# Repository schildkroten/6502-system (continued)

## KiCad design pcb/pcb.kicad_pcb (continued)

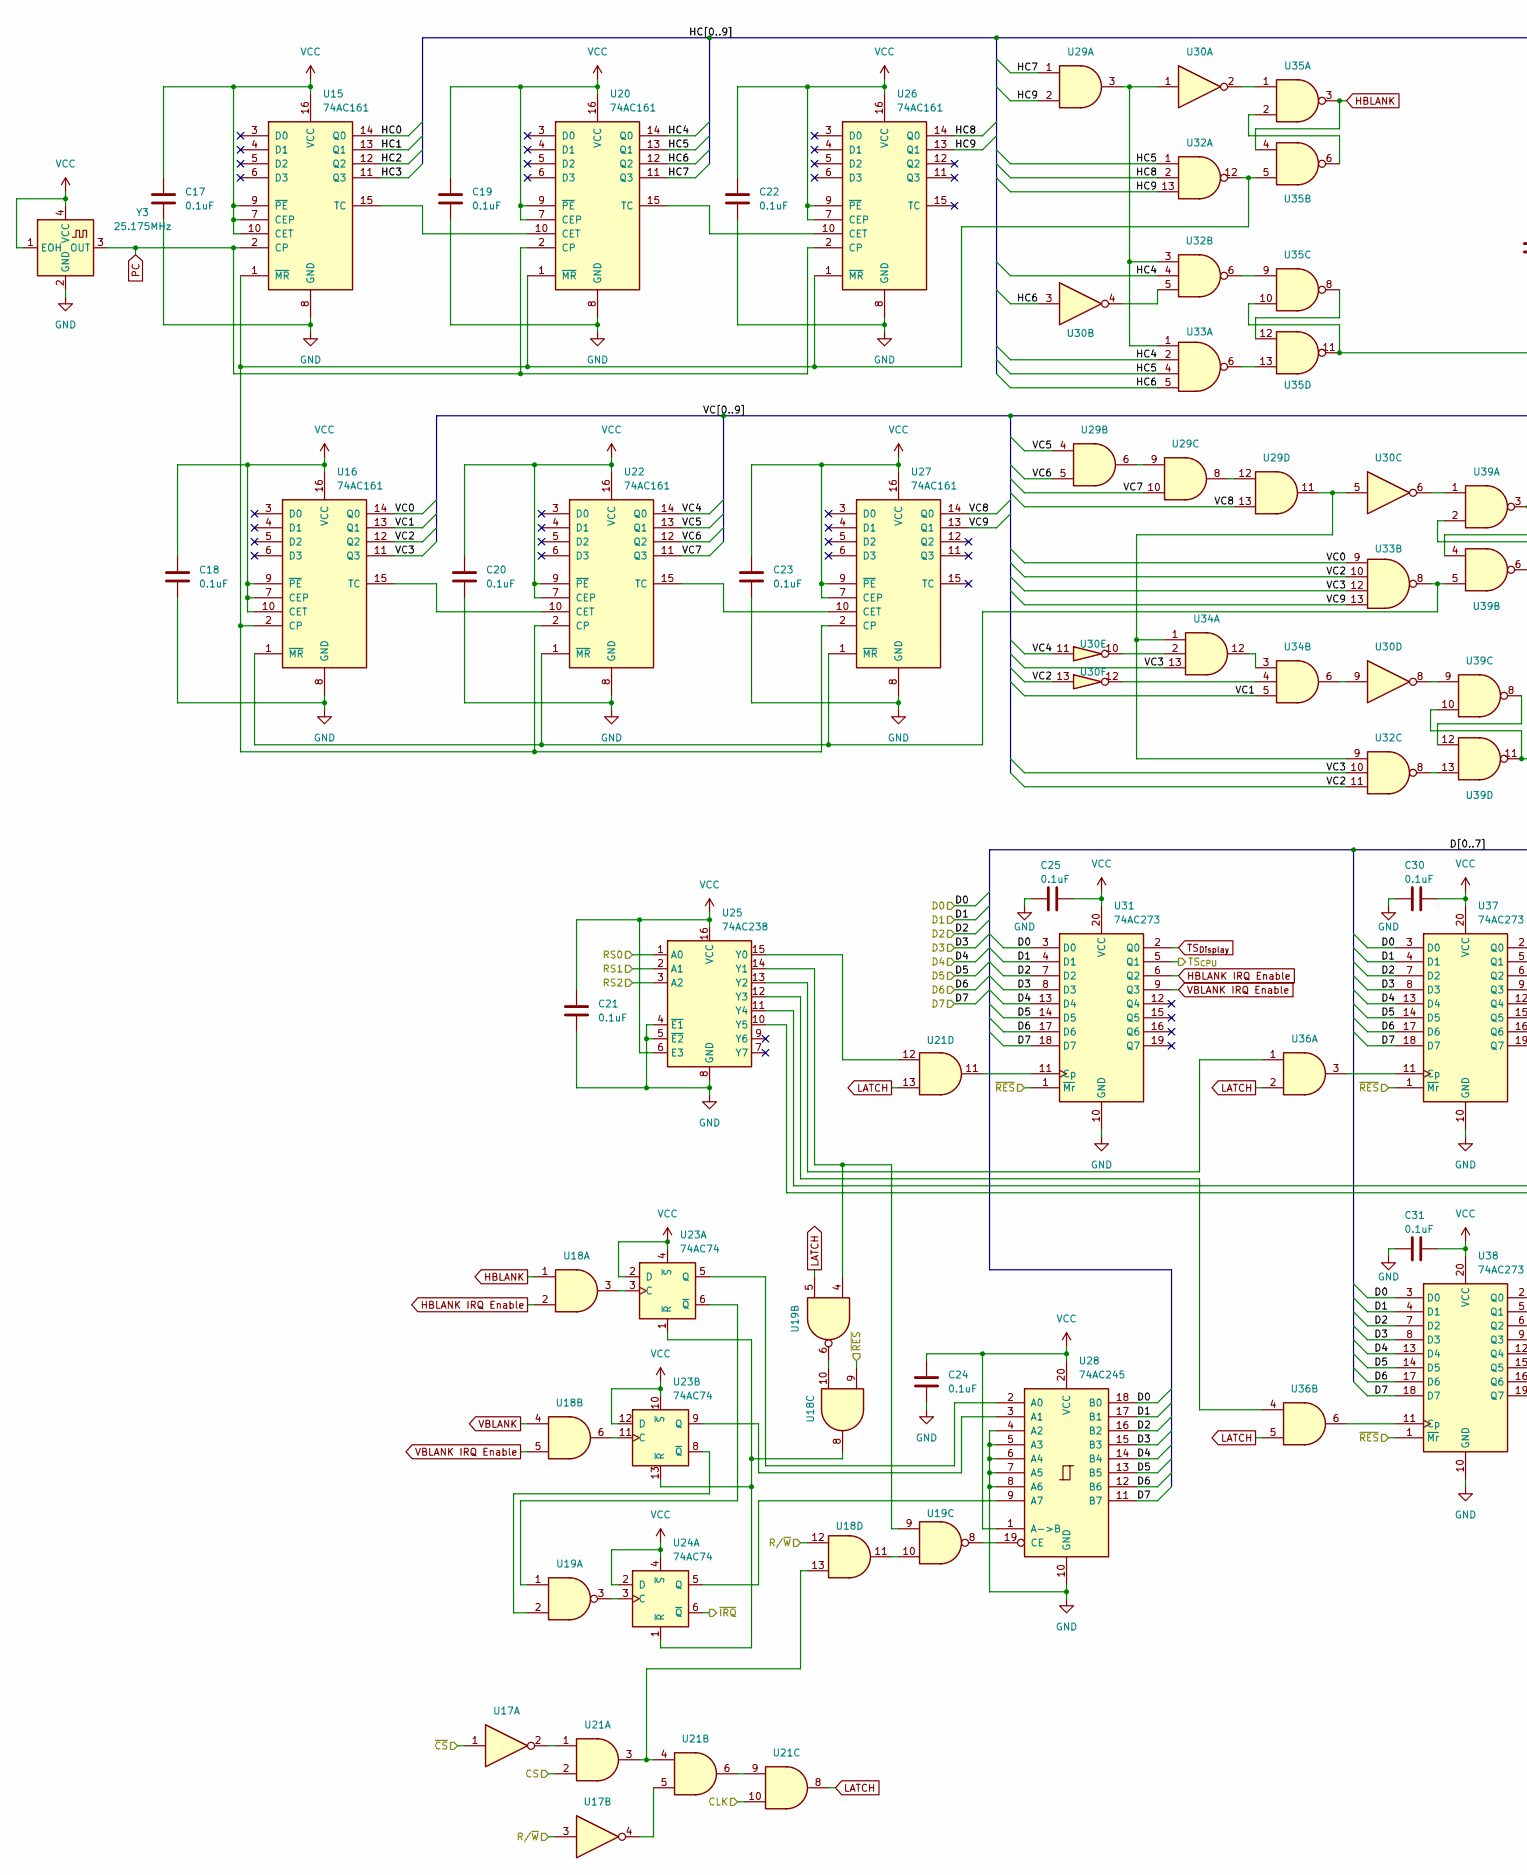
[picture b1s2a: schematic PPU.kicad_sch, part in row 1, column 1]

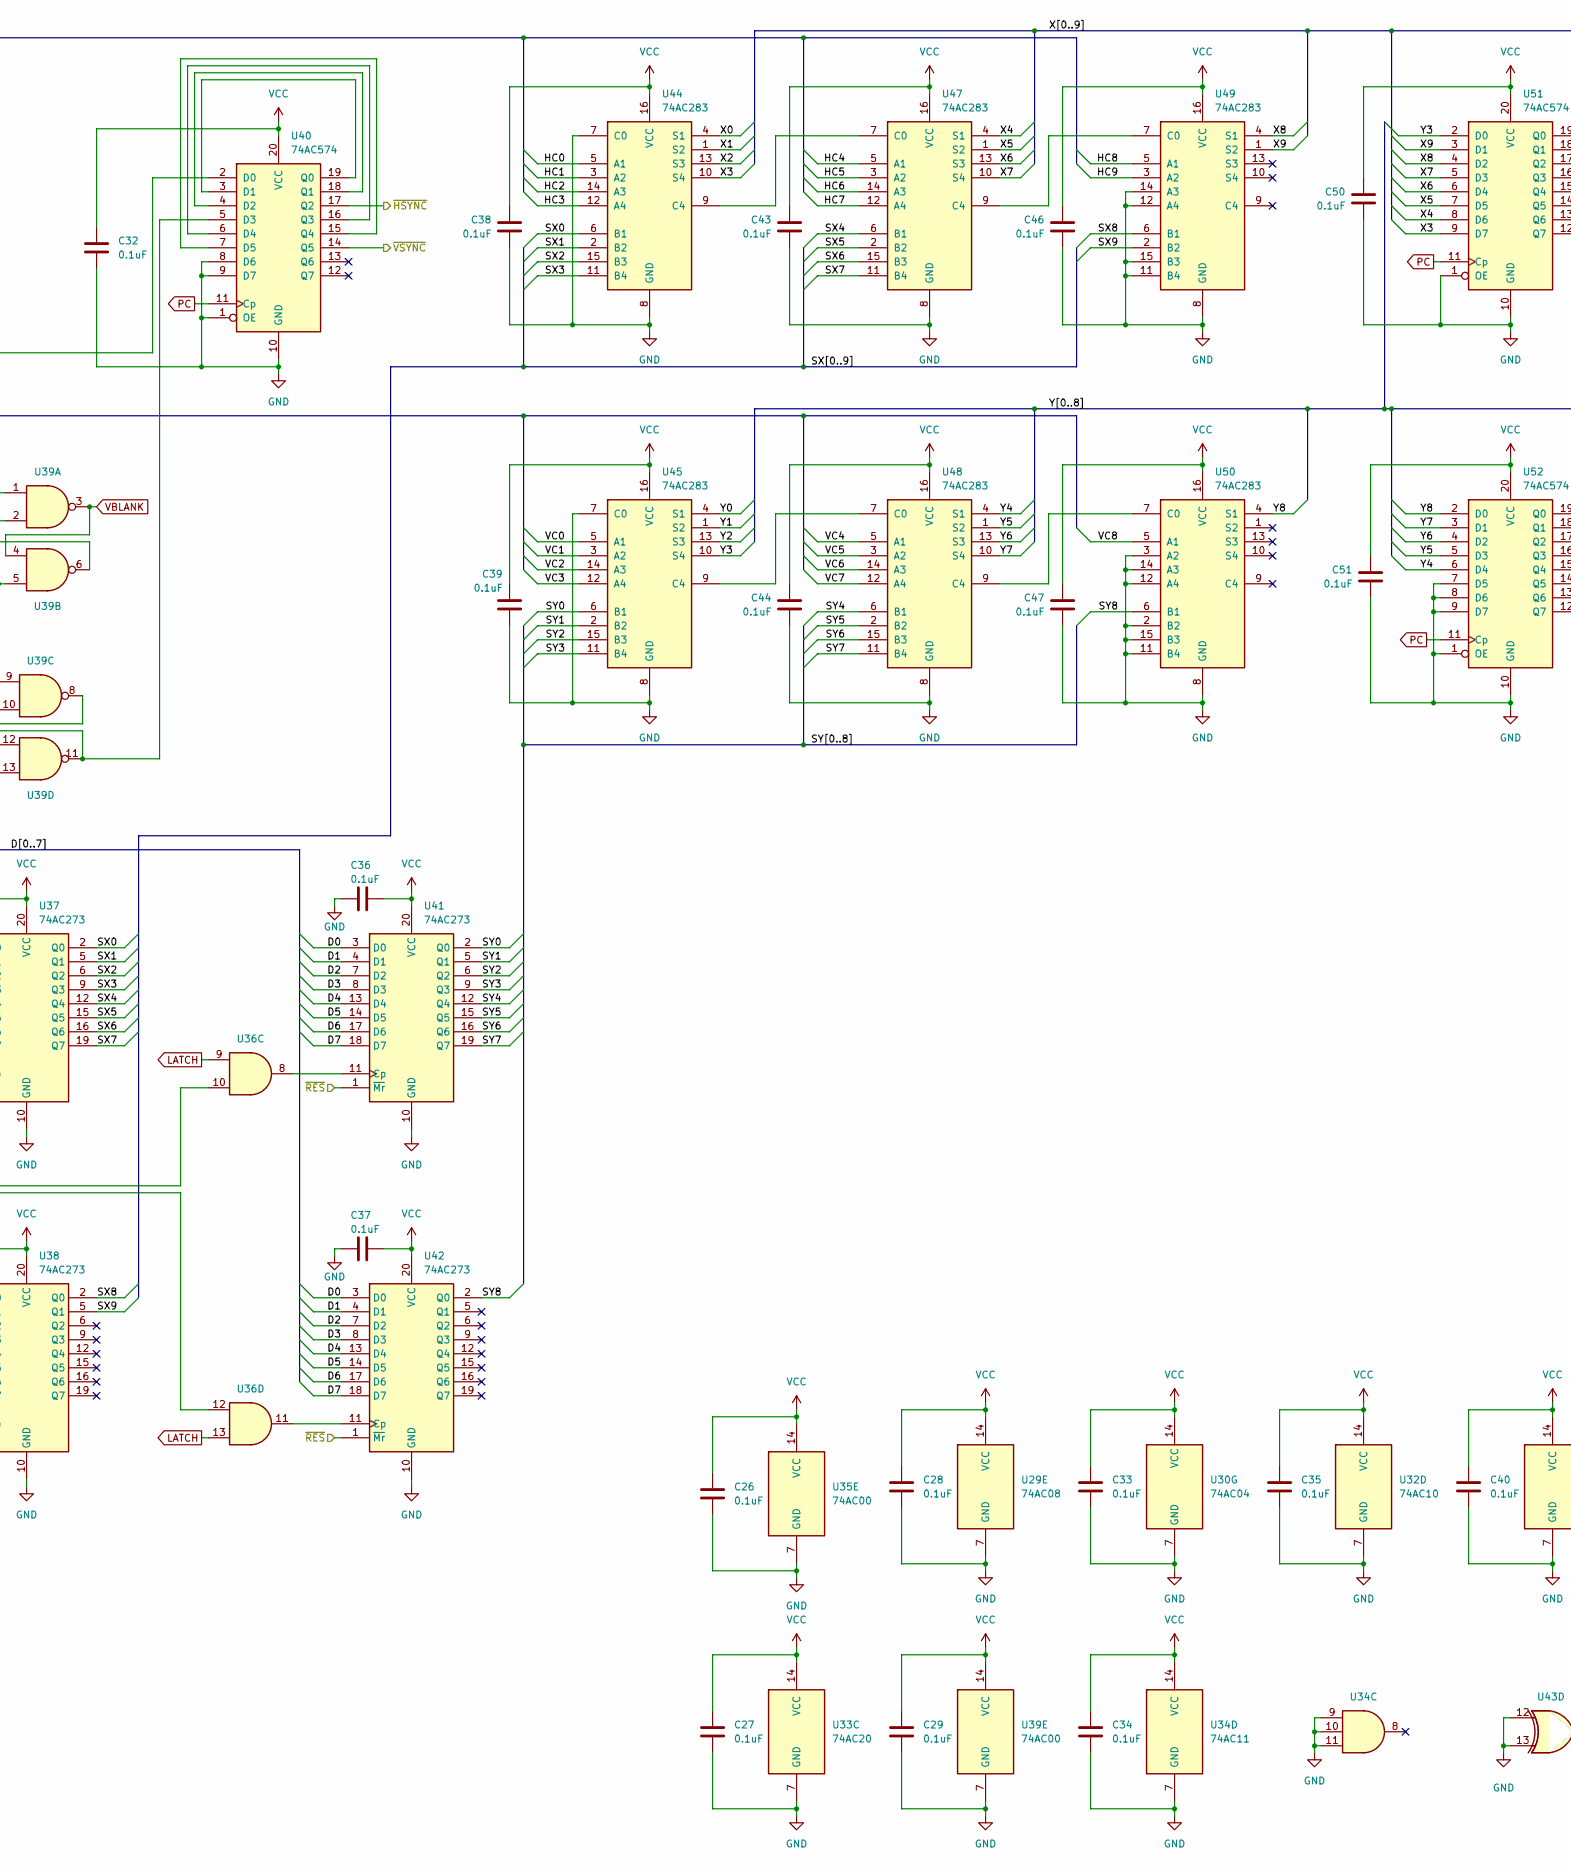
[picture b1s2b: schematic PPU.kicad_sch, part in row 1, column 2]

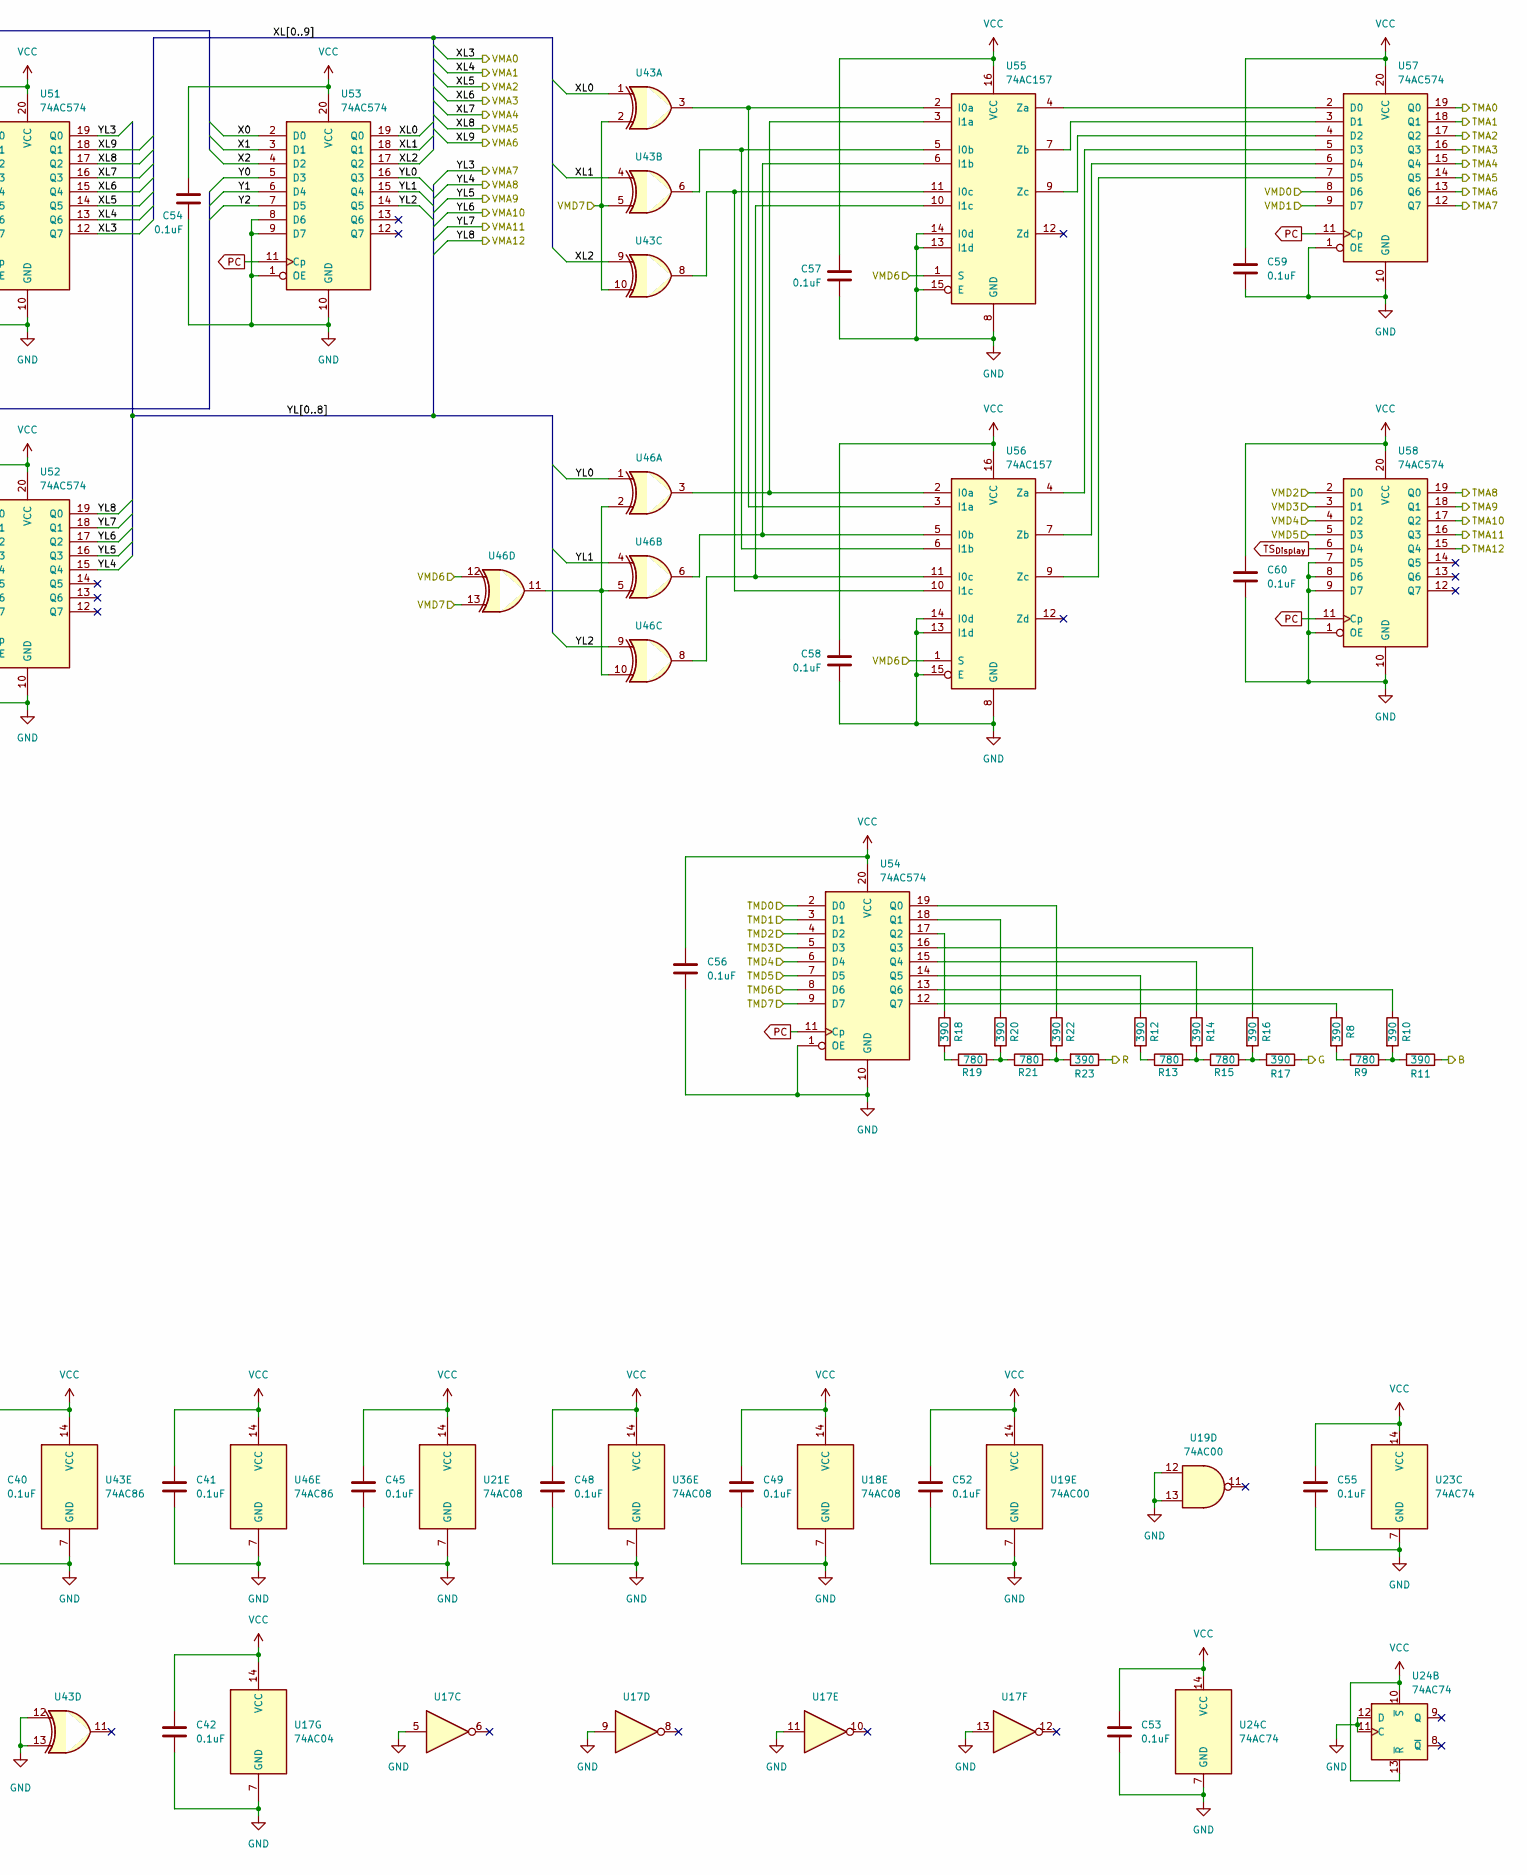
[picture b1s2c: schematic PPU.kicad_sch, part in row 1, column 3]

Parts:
C17, C18, C19, C20, C21, C22, C23, C24, C25, C26, C27, C28, C29, C30, C31, C32, C33, C34, C35, C36, C37, C38, C39, C40, C41, C42, C43, C44, C45, C46, C47, C48, C49, C50, C51, C52, C53, C54, C55, C56, C57, C58, C59, C60: 0.1uF; C_0805_2012Metric
R8, R10, R11, R12, R14, R16, R17, R18, R20, R22, R23: 390; R_0805_2012Metric
R9, R13, R15, R19, R21: 780; R_0805_2012Metric
U15, U16, U20, U22, U26, U27: 74AC161; SOIC-16_3.9x9.9mm_P1.27mm
U17, U30: 74AC04; SOIC-14_3.9x8.7mm_P1.27mm
U18, U21, U29, U36: 74AC08; SOIC-14_3.9x8.7mm_P1.27mm
U19, U35, U39: 74AC00; SOIC-14_3.9x8.7mm_P1.27mm
U23, U24: 74AC74; SOIC-14_3.9x8.7mm_P1.27mm
U25: 74AC238; SOIC-16_3.9x9.9mm_P1.27mm
U28: 74AC245; TSSOP-20_4.4x6.5mm_P0.65mm
U31, U37, U38, U41, U42: 74AC273; SOIC-20W_7.5x12.8mm_P1.27mm
U32: 74AC10; SOIC-14_3.9x8.7mm_P1.27mm
U33: 74AC20; SOIC-14_3.9x8.7mm_P1.27mm
U34: 74AC11; SOIC-14_3.9x8.7mm_P1.27mm
U40, U51, U52, U53, U54, U57, U58: 74AC574; SOIC-20W_7.5x12.8mm_P1.27mm
U43, U46: 74AC86; SOIC-14_3.9x8.7mm_P1.27mm
U44, U45, U47, U48, U49, U50: 74AC283; SOIC-16_3.9x9.9mm_P1.27mm
U55, U56: 74AC157; SOIC-16_3.9x9.9mm_P1.27mm
Y3: 25.175MHz; Oscillator_SMD_SeikoEpson_SG8002CA-4Pin_7.0x5.0mm

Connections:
/A0: U25.1 (A0); also elsewhere on the board
/A1: U25.2 (A1); also elsewhere on the board
/A2: U25.3 (A2); also elsewhere on the board
/D0: U28.18 (B0), U31.3 (D0), U37.3 (D0), U38.3 (D0), U41.3 (D0), U42.3 (D0); also elsewhere on the board
/D1: U28.17 (B1), U31.4 (D1), U37.4 (D1), U38.4 (D1), U41.4 (D1), U42.4 (D1); also elsewhere on the board
/D2: U28.16 (B2), U31.7 (D2), U37.7 (D2), U38.7 (D2), U41.7 (D2), U42.7 (D2); also elsewhere on the board
/D3: U28.15 (B3), U31.8 (D3), U37.8 (D3), U38.8 (D3), U41.8 (D3), U42.8 (D3); also elsewhere on the board
/D4: U28.14 (B4), U31.13 (D4), U37.13 (D4), U38.13 (D4), U41.13 (D4), U42.13 (D4); also elsewhere on the board
/D5: U28.13 (B5), U31.14 (D5), U37.14 (D5), U38.14 (D5), U41.14 (D5), U42.14 (D5); also elsewhere on the board
/D6: U28.12 (B6), U31.17 (D6), U37.17 (D6), U38.17 (D6), U41.17 (D6), U42.17 (D6); also elsewhere on the board
/D7: U28.11 (B7), U31.18 (D7), U37.18 (D7), U38.18 (D7), U41.18 (D7), U42.18 (D7); also elsewhere on the board
/PPU/B: R11.1; also elsewhere on the board
/PPU/G: R17.1; also elsewhere on the board
/PPU/HC0: U15.14 (Q0), U44.5 (A1)
/PPU/HC1: U15.13 (Q1), U44.3 (A2)
/PPU/HC2: U15.12 (Q2), U44.14 (A3)
/PPU/HC3: U15.11 (Q3), U44.12 (A4)
/PPU/HC4: U20.14 (Q0), U32.4, U33.2, U47.5 (A1)
/PPU/HC5: U20.13 (Q1), U32.1, U33.4, U47.3 (A2)
/PPU/HC6: U20.12 (Q2), U30.3, U33.5, U47.14 (A3)
/PPU/HC7: U20.11 (Q3), U29.1, U47.12 (A4)
/PPU/HC8: U26.14 (Q0), U32.2, U49.5 (A1)
/PPU/HC9: U26.13 (Q1), U29.2, U32.13, U49.3 (A2)
/PPU/R: R23.1; also elsewhere on the board
/PPU/SX0: U37.2 (Q0), U44.6 (B1)
/PPU/SX1: U37.5 (Q1), U44.2 (B2)
/PPU/SX2: U37.6 (Q2), U44.15 (B3)
/PPU/SX3: U37.9 (Q3), U44.11 (B4)
/PPU/SX4: U37.12 (Q4), U47.6 (B1)
/PPU/SX5: U37.15 (Q5), U47.2 (B2)
/PPU/SX6: U37.16 (Q6), U47.15 (B3)
/PPU/SX7: U37.19 (Q7), U47.11 (B4)
/PPU/SX8: U38.2 (Q0), U49.6 (B1)
/PPU/SX9: U38.5 (Q1), U49.2 (B2)
/PPU/SY0: U41.2 (Q0), U45.6 (B1)
/PPU/SY1: U41.5 (Q1), U45.2 (B2)
/PPU/SY2: U41.6 (Q2), U45.15 (B3)
/PPU/SY3: U41.9 (Q3), U45.11 (B4)
/PPU/SY4: U41.12 (Q4), U48.6 (B1)
/PPU/SY5: U41.15 (Q5), U48.2 (B2)
/PPU/SY6: U41.16 (Q6), U48.15 (B3)
/PPU/SY7: U41.19 (Q7), U48.11 (B4)
/PPU/SY8: U42.2 (Q0), U50.6 (B1)
/PPU/TS_{CPU}: U31.5 (Q1); also elsewhere on the board
/PPU/VC0: U16.14 (Q0), U33.9, U45.5 (A1)
/PPU/VC1: U16.13 (Q1), U34.5, U45.3 (A2)
/PPU/VC2: U16.12 (Q2), U30.13, U32.11, U33.10, U45.14 (A3)
/PPU/VC3: U16.11 (Q3), U32.10, U33.12, U34.13, U45.12 (A4)
/PPU/VC4: U22.14 (Q0), U30.11, U48.5 (A1)
/PPU/VC5: U22.13 (Q1), U29.4, U48.3 (A2)
/PPU/VC6: U22.12 (Q2), U29.5, U48.14 (A3)
/PPU/VC7: U22.11 (Q3), U29.10, U48.12 (A4)
/PPU/VC8: U27.14 (Q0), U29.13, U50.5 (A1)
/PPU/VC9: U27.13 (Q1), U33.13
/PPU/X0: U44.4 (S1), U53.2 (D0)
/PPU/X1: U44.1 (S2), U53.3 (D1)
/PPU/X2: U44.13 (S3), U53.4 (D2)
/PPU/X3: U44.10 (S4), U51.9 (D7)
/PPU/X4: U47.4 (S1), U51.8 (D6)
/PPU/X5: U47.1 (S2), U51.7 (D5)
/PPU/X6: U47.13 (S3), U51.6 (D4)
/PPU/X7: U47.10 (S4), U51.5 (D3)
/PPU/X8: U49.4 (S1), U51.4 (D2)
/PPU/X9: U49.1 (S2), U51.3 (D1)
/PPU/XL0: U43.1, U53.19 (Q0)
/PPU/XL1: U43.4, U53.18 (Q1)
/PPU/XL2: U43.9, U53.17 (Q2)
/PPU/Y0: U45.4 (S1), U53.5 (D3)
/PPU/Y1: U45.1 (S2), U53.6 (D4)
/PPU/Y2: U45.13 (S3), U53.7 (D5)
/PPU/Y3: U45.10 (S4), U51.2 (D0)
/PPU/Y4: U48.4 (S1), U52.6 (D4)
/PPU/Y5: U48.1 (S2), U52.5 (D3)
/PPU/Y6: U48.13 (S3), U52.4 (D2)
/PPU/Y7: U48.10 (S4), U52.3 (D1)
/PPU/Y8: U50.4 (S1), U52.2 (D0)
/PPU/YL0: U46.1, U53.16 (Q3)
/PPU/YL1: U46.4, U53.15 (Q4)
/PPU/YL2: U46.9, U53.14 (Q5)
/PPU/~HSYNC: U40.17 (Q2); also elsewhere on the board
/PPU/~VSYNC: U40.14 (Q5); also elsewhere on the board
/TMA0: U57.19 (Q0); also elsewhere on the board
/TMA1: U57.18 (Q1); also elsewhere on the board
/TMA2: U57.17 (Q2); also elsewhere on the board
/TMA3: U57.16 (Q3); also elsewhere on the board
/TMA4: U57.15 (Q4); also elsewhere on the board
/TMA5: U57.14 (Q5); also elsewhere on the board
/TMA6: U57.13 (Q6); also elsewhere on the board
/TMA7: U57.12 (Q7); also elsewhere on the board
/TMA8: U58.19 (Q0); also elsewhere on the board
/TMA9: U58.18 (Q1); also elsewhere on the board
/TMA10: U58.17 (Q2); also elsewhere on the board
/TMA11: U58.16 (Q3); also elsewhere on the board
/TMA12: U58.15 (Q4); also elsewhere on the board
/TMD0: U54.2 (D0); also elsewhere on the board
/TMD1: U54.3 (D1); also elsewhere on the board
/TMD2: U54.4 (D2); also elsewhere on the board
/TMD3: U54.5 (D3); also elsewhere on the board
/TMD4: U54.6 (D4); also elsewhere on the board
/TMD5: U54.7 (D5); also elsewhere on the board
/TMD6: U54.8 (D6); also elsewhere on the board
/TMD7: U54.9 (D7); also elsewhere on the board
/VMA0: U51.12 (Q7); also elsewhere on the board
/VMA1: U51.13 (Q6); also elsewhere on the board
/VMA2: U51.14 (Q5); also elsewhere on the board
/VMA3: U51.15 (Q4); also elsewhere on the board
/VMA4: U51.16 (Q3); also elsewhere on the board
/VMA5: U51.17 (Q2); also elsewhere on the board
/VMA6: U51.18 (Q1); also elsewhere on the board
/VMA7: U51.19 (Q0); also elsewhere on the board
/VMA8: U52.15 (Q4); also elsewhere on the board
/VMA9: U52.16 (Q3); also elsewhere on the board
/VMA10: U52.17 (Q2); also elsewhere on the board
/VMA11: U52.18 (Q1); also elsewhere on the board
/VMA12: U52.19 (Q0); also elsewhere on the board
/VMD0: U57.8 (D6); also elsewhere on the board
/VMD1: U57.9 (D7); also elsewhere on the board
/VMD2: U58.2 (D0); also elsewhere on the board
/VMD3: U58.3 (D1); also elsewhere on the board
/VMD4: U58.4 (D2); also elsewhere on the board
/VMD5: U58.5 (D3); also elsewhere on the board
/VMD6: U46.12, U55.1 (S), U56.1 (S); also elsewhere on the board
/VMD7: U43.2, U43.5, U43.10, U46.13; also elsewhere on the board
CLK: U21.10; also elsewhere on the board
CS_{PPU}: U21.2; also elsewhere on the board
GND: C17.2, C18.2, C19.2, C20.2, C21.2, C22.2, C23.2, C24.2, C25.2, C26.2, C27.2, C28.2, C29.2, C30.2, C31.2, C32.2, C33.2, C34.2, C35.2, C36.2, C37.2, C38.2, C39.2, C40.2, C41.2, C42.2, C43.2, C44.2, C45.2, C46.2, C47.2, C48.2, C49.2, C50.2, C51.2, C52.2, C53.2, C54.2, C55.2, C56.2, C57.2, C58.2, C59.2, C60.2, U15.8 (GND), U16.8 (GND), U17.5, U17.7 (GND), U17.9, U17.11, U17.13, U18.7 (GND), U19.7 (GND), U19.12, U19.13, U20.8 (GND), U21.7 (GND), U22.8 (GND), U23.7 (GND), U24.7 (GND), U24.11 (C), U24.12 (D), U25.4 (~E1), U25.5 (~E2), U25.8 (GND), U26.8 (GND), U27.8 (GND), U28.4 (A2), U28.5 (A3), U28.6 (A4), U28.7 (A5), U28.8 (A6), U28.10 (GND), U29.7 (GND), U30.7 (GND), U31.10 (GND), U32.7 (GND), U33.7 (GND), U34.7 (GND), U34.9, U34.10, U34.11, U35.7 (GND), U36.7 (GND), U37.10 (GND), U38.10 (GND), U39.7 (GND), U40.1 (OE), U40.8 (D6), U40.9 (D7), U40.10 (GND), U41.10 (GND), U42.10 (GND), U43.7 (GND), U43.12, U43.13, U44.7 (C0), U44.8 (GND), U45.7 (C0), U45.8 (GND), U46.7 (GND), U47.8 (GND), U48.8 (GND), U49.8 (GND), U49.11 (B4), U49.12 (A4), U49.14 (A3), U49.15 (B3), U50.2 (B2), U50.3 (A2), U50.8 (GND), U50.11 (B4), U50.12 (A4), U50.14 (A3), U50.15 (B3), U51.1 (OE), U51.10 (GND), U52.1 (OE), U52.7 (D5), U52.8 (D6), U52.9 (D7), U52.10 (GND), U53.1 (OE), U53.8 (D6), U53.9 (D7), U53.10 (GND), U54.1 (OE), U54.10 (GND), U55.8 (GND), U55.13 (I1d), U55.14 (I0d), U55.15 (E), U56.8 (GND), U56.13 (I1d), U56.14 (I0d), U56.15 (E), U57.1 (OE), U57.10 (GND), U58.1 (OE), U58.7 (D5), U58.8 (D6), U58.9 (D7), U58.10 (GND), Y3.2 (GND); also elsewhere on the board
HBLANK: U18.1, U35.3, U35.4
HBLANK IRQ Enable: U18.2, U31.6 (Q2)
LATCH: U19.5, U21.8, U21.13, U36.2, U36.5, U36.9, U36.13
unnamed: R8.2, R9.1
unnamed: R9.2, R10.2, R11.2
unnamed: R12.2, R13.1
unnamed: R13.2, R14.2, R15.1
unnamed: R15.2, R16.2, R17.2
unnamed: R18.2, R19.1
unnamed: R19.2, R20.2, R21.1
unnamed: R21.2, R22.2, R23.2
unnamed: U15.15 (TC), U20.10 (CET)
unnamed: U15.1 (~MR), U16.2 (CP), U20.1 (~MR), U22.2 (CP), U26.1 (~MR), U27.2 (CP), U32.12, U35.5
unnamed: U16.15 (TC), U22.10 (CET)
unnamed: U16.1 (~MR), U22.1 (~MR), U27.1 (~MR), U33.8, U39.5
unnamed: U17.2, U21.1
unnamed: U17.4, U21.5
unnamed: U18.10, U19.6
unnamed: U18.11, U19.10
unnamed: U18.13, U21.3, U21.4
unnamed: U20.15 (TC), U26.10 (CET)
unnamed: U21.6, U21.9
unnamed: U22.15 (TC), U27.10 (CET)
unnamed: U18.3, U23.3 (C)
unnamed: U23.5 (Q), U28.2 (A0)
unnamed: U19.1, U23.6 (~Q)
unnamed: U18.8, U23.1 (~R), U23.13 (~R), U24.1 (~R)
unnamed: U18.6, U23.11 (C)
unnamed: U23.9 (Q), U28.3 (A1)
unnamed: U19.2, U23.8 (~Q)
unnamed: U19.3, U24.3 (C)
unnamed: U24.5 (Q), U28.9 (A7)
unnamed: U21.12, U25.15 (Y0)
unnamed: U19.4, U19.9, U25.14 (Y1)
unnamed: U25.13 (Y2), U36.1
unnamed: U25.12 (Y3), U36.4
unnamed: U25.11 (Y4), U36.10
unnamed: U25.10 (Y5), U36.12
unnamed: U19.8, U28.19 (CE)
unnamed: U29.3, U30.1, U32.3, U33.1
unnamed: U29.6, U29.9
unnamed: U29.11, U30.5, U32.9, U34.1
unnamed: U29.8, U29.12
unnamed: U30.2, U35.1
unnamed: U30.4, U32.5
unnamed: U30.6, U39.1
unnamed: U30.8, U39.9
unnamed: U30.9, U34.6
unnamed: U30.10, U34.2
unnamed: U30.12, U34.4
unnamed: U21.11, U31.11 (Cp)
unnamed: U32.6, U35.9
unnamed: U32.8, U39.13
unnamed: U33.6, U35.13
unnamed: U34.3, U34.12
unnamed: U35.2, U35.6
unnamed: U35.8, U35.12
unnamed: U36.3, U37.11 (Cp)
unnamed: U36.6, U38.11 (Cp)
unnamed: U39.2, U39.6
unnamed: U39.8, U39.12
unnamed: U35.10, U35.11, U40.2 (D0)
unnamed: U40.3 (D1), U40.19 (Q0)
unnamed: U40.4 (D2), U40.18 (Q1)
unnamed: U39.10, U39.11, U40.5 (D3)
unnamed: U40.6 (D4), U40.16 (Q3)
unnamed: U40.7 (D5), U40.15 (Q4)
unnamed: U36.8, U41.11 (Cp)
unnamed: U36.11, U42.11 (Cp)
unnamed: U44.9 (C4), U47.7 (C0)
unnamed: U45.9 (C4), U48.7 (C0)
unnamed: U46.2, U46.5, U46.10, U46.11
unnamed: U47.9 (C4), U49.7 (C0)
unnamed: U48.9 (C4), U50.7 (C0)
unnamed: R22.1, U54.19 (Q0)
unnamed: R20.1, U54.18 (Q1)
unnamed: R18.1, U54.17 (Q2)
unnamed: R16.1, U54.16 (Q3)
unnamed: R14.1, U54.15 (Q4)
unnamed: R12.1, U54.14 (Q5)
unnamed: R10.1, U54.13 (Q6)
unnamed: R8.1, U54.12 (Q7)
unnamed: U43.3, U55.2 (I0a), U56.3 (I1a)
unnamed: U43.6, U55.5 (I0b), U56.6 (I1b)
unnamed: U43.8, U55.11 (I0c), U56.10 (I1c)
unnamed: U46.3, U55.3 (I1a), U56.2 (I0a)
unnamed: U46.6, U55.6 (I1b), U56.5 (I0b)
unnamed: U46.8, U55.10 (I1c), U56.11 (I0c)
unnamed: U55.4 (Za), U57.2 (D0)
unnamed: U55.7 (Zb), U57.3 (D1)
unnamed: U55.9 (Zc), U57.4 (D2)
unnamed: U56.4 (Za), U57.5 (D3)
unnamed: U56.7 (Zb), U57.6 (D4)
unnamed: U56.9 (Zc), U57.7 (D5)
PC: U15.2 (CP), U20.2 (CP), U26.2 (CP), U40.11 (Cp), U51.11 (Cp), U52.11 (Cp), U53.11 (Cp), U54.11 (Cp), U57.11 (Cp), U58.11 (Cp), Y3.3 (OUT)
R/~W: U17.3, U18.12; also elsewhere on the board
TS_{Display}: U31.2 (Q0), U58.6 (D4)
VBLANK: U18.4, U39.3, U39.4
VBLANK IRQ Enable: U18.5, U31.9 (Q3)
VCC: C17.1, C18.1, C19.1, C20.1, C21.1, C22.1, C23.1, C24.1, C25.1, C26.1, C27.1, C28.1, C29.1, C30.1, C31.1, C32.1, C33.1, C34.1, C35.1, C36.1, C37.1, C38.1, C39.1, C40.1, C41.1, C42.1, C43.1, C44.1, C45.1, C46.1, C47.1, C48.1, C49.1, C50.1, C51.1, C52.1, C53.1, C54.1, C55.1, C56.1, C57.1, C58.1, C59.1, C60.1, U15.7 (CEP), U15.9 (~PE), U15.10 (CET), U15.16 (VCC), U16.7 (CEP), U16.9 (~PE), U16.10 (CET), U16.16 (VCC), U17.14 (VCC), U18.14 (VCC), U19.14 (VCC), U20.7 (CEP), U20.9 (~PE), U20.16 (VCC), U21.14 (VCC), U22.7 (CEP), U22.9 (~PE), U22.16 (VCC), U23.2 (D), U23.4 (~S), U23.10 (~S), U23.12 (D), U23.14 (VCC), U24.2 (D), U24.4 (~S), U24.10 (~S), U24.13 (~R), U24.14 (VCC), U25.6 (E3), U25.16 (VCC), U26.7 (CEP), U26.9 (~PE), U26.16 (VCC), U27.7 (CEP), U27.9 (~PE), U27.16 (VCC), U28.1 (A->B), U28.20 (VCC), U29.14 (VCC), U30.14 (VCC), U31.20 (VCC), U32.14 (VCC), U33.14 (VCC), U34.14 (VCC), U35.14 (VCC), U36.14 (VCC), U37.20 (VCC), U38.20 (VCC), U39.14 (VCC), U40.20 (VCC), U41.20 (VCC), U42.20 (VCC), U43.14 (VCC), U44.16 (VCC), U45.16 (VCC), U46.14 (VCC), U47.16 (VCC), U48.16 (VCC), U49.16 (VCC), U50.16 (VCC), U51.20 (VCC), U52.20 (VCC), U53.20 (VCC), U54.20 (VCC), U55.16 (VCC), U56.16 (VCC), U57.20 (VCC), U58.20 (VCC), Y3.1 (EOH), Y3.4 (VCC); also elsewhere on the board
~CS_{IO}: U17.1; also elsewhere on the board
~IRQ_{PPU}: U24.6 (~Q); also elsewhere on the board
~RES: U18.9, U31.1 (~Mr), U37.1 (~Mr), U38.1 (~Mr), U41.1 (~Mr), U42.1 (~Mr); also elsewhere on the board

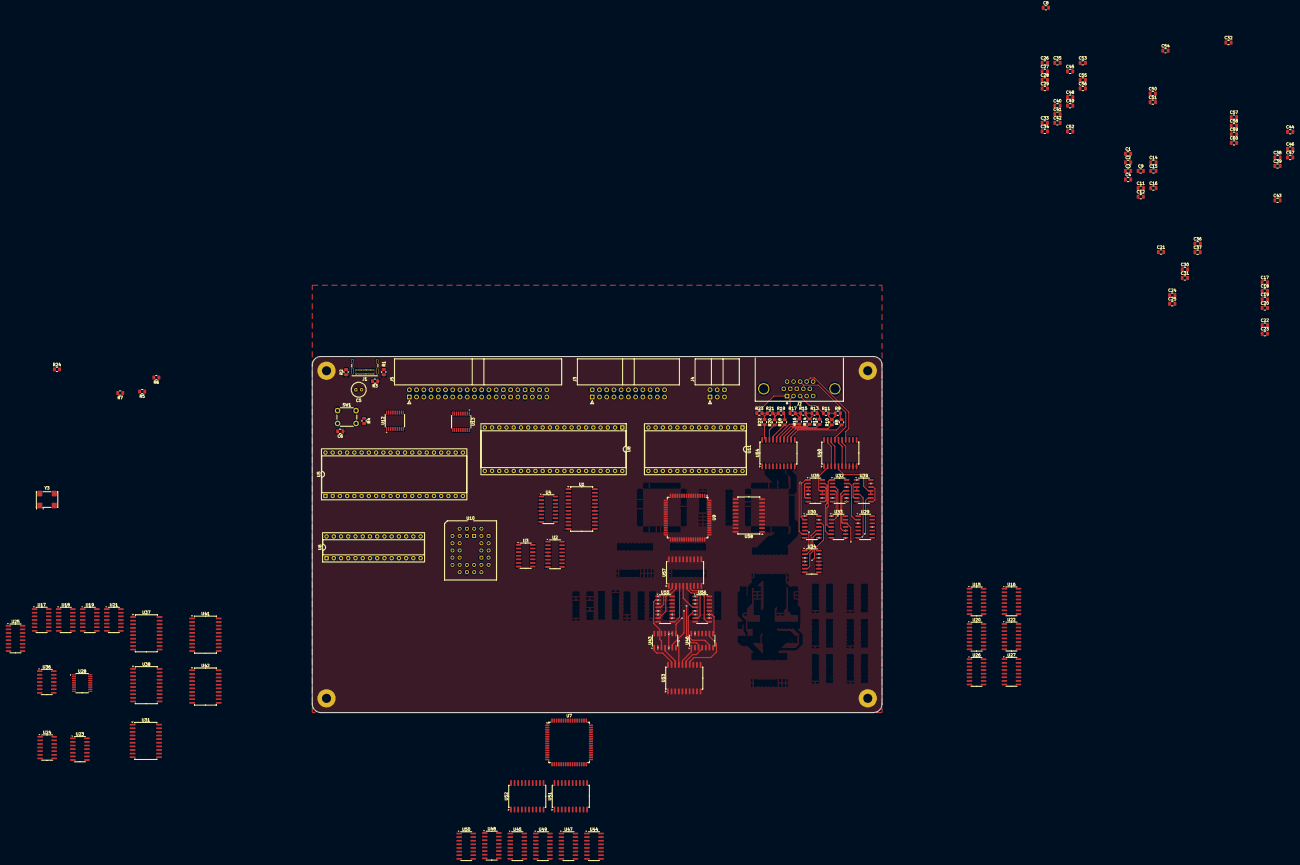
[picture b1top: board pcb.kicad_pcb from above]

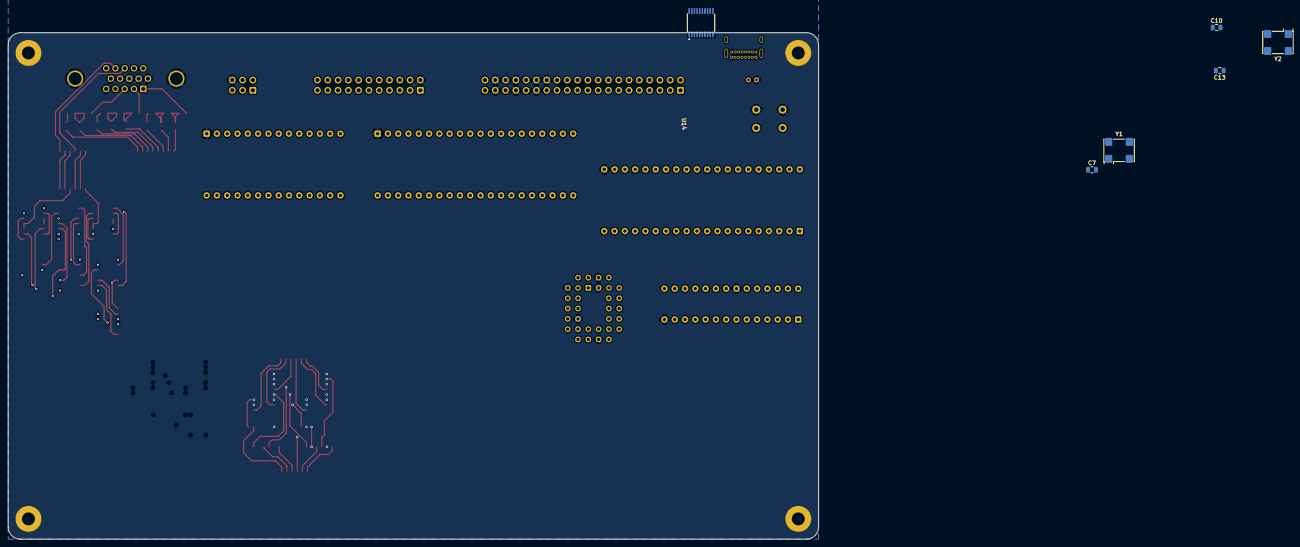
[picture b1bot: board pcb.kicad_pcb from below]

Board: 6 copper layers, 200.0 x 125.0 mm, 155 parts (6 on the bottom side), 313 nets.

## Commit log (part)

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2025-08-28 added symbols to schematic
2025-10-10 lots of updates
2025-10-10 added silkscreen
2025-10-12 updated .gitignore
2025-10-12 updated library
2025-11-15 Finished vesrsion 1 of the project
2025-12-05 started working on version 2.0
